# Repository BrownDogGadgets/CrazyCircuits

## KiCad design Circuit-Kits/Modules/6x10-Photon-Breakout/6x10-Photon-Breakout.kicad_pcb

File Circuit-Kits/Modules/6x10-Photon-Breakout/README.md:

<!--- start title --->
# 6x10 Photon Breakout Module v1.0
A Lego-compatible Crazy Circuits module

- Updated: 31 Jul 2018
- Website: http://browndoggadgets.com/
- Company: Brown Dog Gadgets
- License: All rights reserved.
<!--- end title --->

This breakout board is for use with the Particle Photon V016 and all pin-compatible boards. 

Powering it from the USB cable will output 5V and 3.3V. There are four three-pin servo headers.   

We recommend buying one 20-pin Harwin connector (P/N [M20-9992046](https://www.digikey.com/products/en?keywords=M20-9992046)) and breaking it into pieces to place the six male headers.

<!--- bom start --->
### Bill of Materials

|Ref|Qty|Description|Digikey PN|
|---|---|-----------|------|
|U1|1|PARTICLE PHOTON V016|1878-1000-ND|

<!--- bom end --->

### Manufacturing Notes

This board must be v-scored. Do not panelize with support tabs or mousebites.

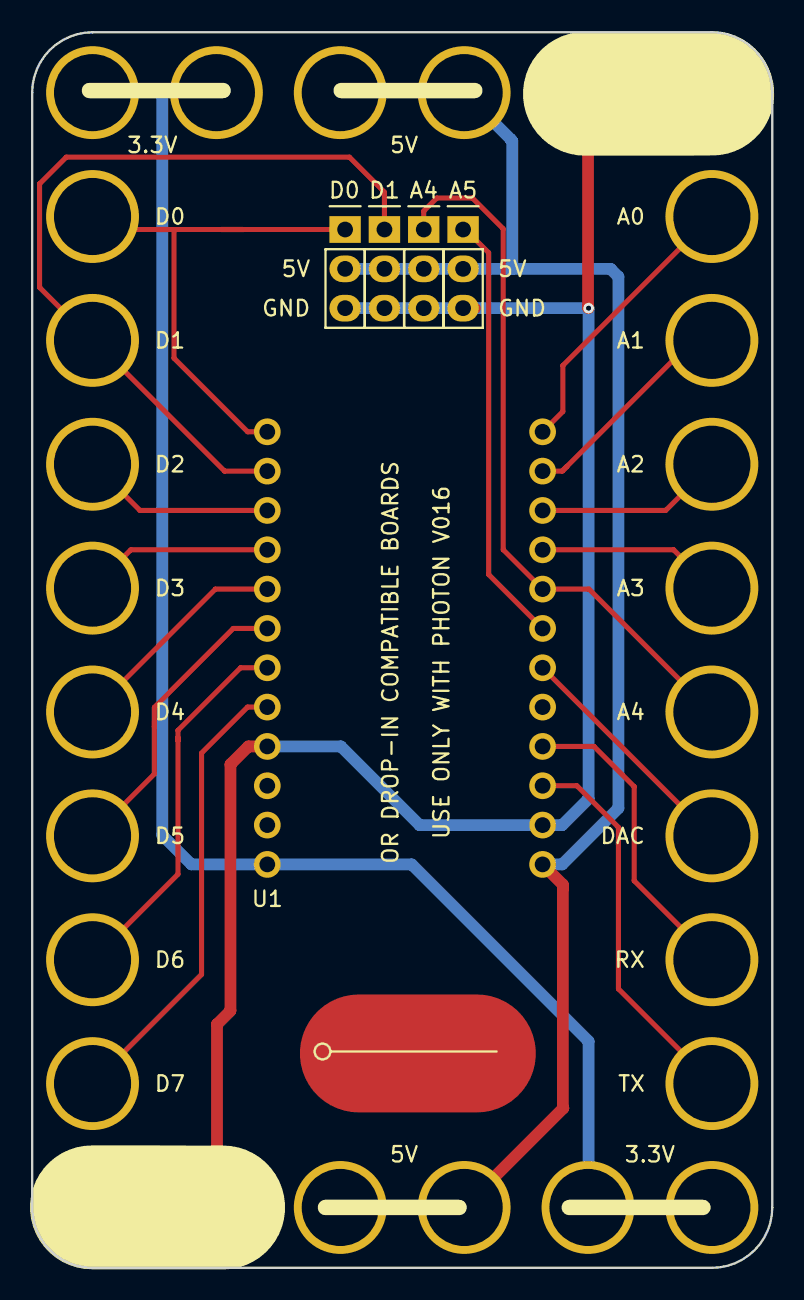
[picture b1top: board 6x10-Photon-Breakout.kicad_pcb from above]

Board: 2 copper layers, 47.8 x 79.8 mm, 6 parts (0 on the bottom side), 6 nets.

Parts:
J1, J2, J3: PWM; CONN-HEADER-STRAIGHT-P2.54MM-1x03
J4: Breakout; CONN-HEADER-STRAIGHT-P2.54MM-1x03
LOGO: BROWN DOG; LOGO-CRAZY-1x2
U1: PARTICLE-PHOTON-V016; PHOTON-V016-6x10

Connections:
5V: J1.VIN, J2.VIN, J3.VIN, J4.VIN, U1.5V, U1.VIN
/A4: J3.A4, U1.A4
/A5: J4.A5, U1.A5
/D0: J1.D0, U1.D0
/D1: J2.D1, U1.D1
GND: J1.GND, J2.GND, J3.GND, J4.GND, U1.GND

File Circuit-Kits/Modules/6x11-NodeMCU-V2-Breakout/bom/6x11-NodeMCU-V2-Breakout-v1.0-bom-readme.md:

|Ref|Qty|Description|Banggood PN|
|---|---|-----------|------|
|U1|1|NODEMCU LUA V2 ESP-12E DEV KIT|1097112|


|Ref|Qty|Description|Digikey PN|
|---|---|-----------|------|
|J1 J2 J3 J4|4|HEADER MALE 3POS TH 1x03 0.1IN|952-1902-ND|

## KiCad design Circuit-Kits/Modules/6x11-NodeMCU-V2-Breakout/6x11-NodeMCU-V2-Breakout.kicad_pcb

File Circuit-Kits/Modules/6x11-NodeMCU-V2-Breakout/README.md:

<!--- start title --->
# 6x11 NodeMCU V2 Breakout Module v1.0
A Lego-compatible Crazy Circuits module

- Updated: 18 Jul 2018

- Website: http://browndoggadgets.com/
- Company: Brown Dog Gadgets
- License: All rights reserved.
<!--- end title --->

The NodeMCU project calls this version of the board v1.0, but it's commonly called the V2 in production. 

This is the vendor we used: [Banggood P/N 1097112](https://www.banggood.com/NodeMcu-Lua-WIFI-Internet-Things-Development-Board-Based-ESP8266-CP2102-Wireless-Module-p-1097112.html)

Here's the documentation from NodeMCU, including a handy pinout diagram: [NodeMCU v1.0 docs](https://github.com/nodemcu/nodemcu-devkit-v1.0)

The module can be powered by plugging in USB or by applying 5V to the VIN input pin on the lower left. Don't expect to pull 5V out of the module: 5V is input only. This is a 3.3V module.

<!--- bom start --->
### Bill of Materials

|Ref|Qty|Description|Banggood PN|
|---|---|-----------|------|
|U1|1|NODEMCU LUA V2 ESP-12E DEV KIT|1097112|

|Ref|Qty|Description|Digikey PN|
|---|---|-----------|------|
|J1 J2 J3 J4|4|HEADER MALE 3POS TH 1x03 0.1IN|952-1902-ND|

<!--- bom end --->

### Manufacturing Notes

This board must be v-scored. Do not panelize with support tabs or mousebites.

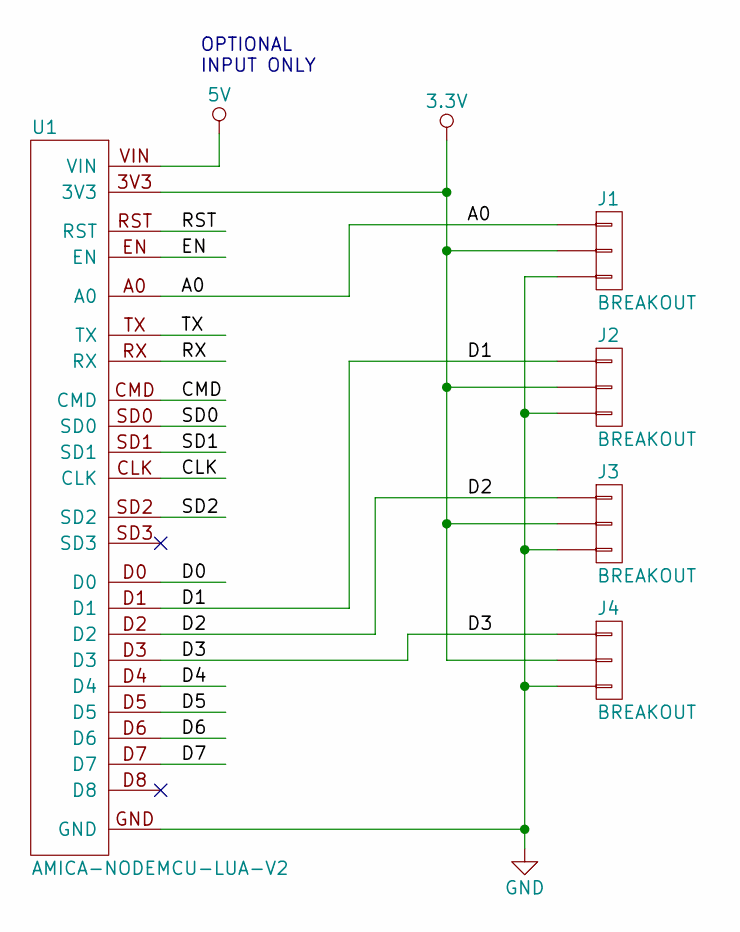
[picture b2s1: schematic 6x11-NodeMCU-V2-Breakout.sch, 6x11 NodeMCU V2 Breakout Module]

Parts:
J1, J2, J3, J4: BREAKOUT; CONN-HEADER-STRAIGHT-P2.54MM-1x03
U1: AMICA-NODEMCU-LUA-V2; NODEMCU-V2-6x11

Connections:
3.3V: J1.2, J2.2, J3.2, J4.2, U1.3V3
5V: U1.VIN
/A0: J1.1, U1.A0
/CLK: U1.CLK
/CMD: U1.CMD
/D0: U1.D0
/D1: J2.1, U1.D1
/D2: J3.1, U1.D2
/D3: J4.1, U1.D3
/D4: U1.D4
/D5: U1.D5
/D6: U1.D6
/D7: U1.D7
/EN: U1.EN
/RST: U1.RST
/RX: U1.RX
/SD0: U1.SD0
/SD1: U1.SD1
/SD2: U1.SD2
/TX: U1.TX
GND: J1.3, J2.3, J3.3, J4.3, U1.GND

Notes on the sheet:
OPTIONAL INPUT ONLY

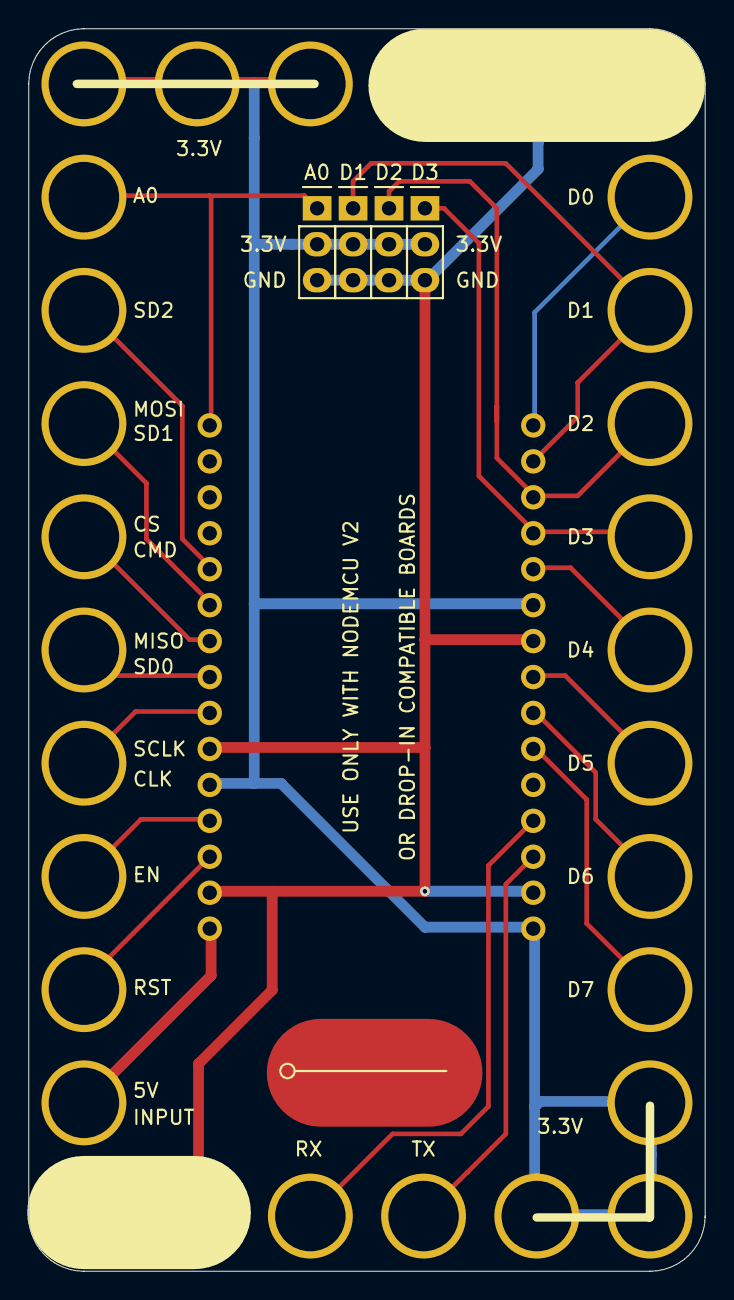
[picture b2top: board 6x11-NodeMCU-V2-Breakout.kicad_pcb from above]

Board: 2 copper layers, 47.8 x 87.8 mm, 6 parts (0 on the bottom side), 6 nets.

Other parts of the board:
LOGO: BROWN DOG; LOGO-CRAZY-1x2

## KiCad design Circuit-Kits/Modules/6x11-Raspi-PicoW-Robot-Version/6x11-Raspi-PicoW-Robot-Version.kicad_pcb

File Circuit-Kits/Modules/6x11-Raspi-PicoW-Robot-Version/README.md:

<!--- start title --->
# 5x11 Raspberry Pi PicoW Robot Breakout v1.6
A Lego-compatible Crazy Circuits module

- Updated: 24 Sep 2018
- Website: http://browndoggadgets.com/
- Company: Brown Dog Gadgets
- License: CERN Open Hardware License v1.2.
<!--- end title --->

This robot controller module comes with an Arduino Nano, four servo headers, and two analog headers. 

We recommend buying two 20-pin Harwin connectors (P/N [M20-9992046](https://www.digikey.com/products/en?keywords=M20-9992046)) and breaking it into pieces to place the six male headers.

<!--- bom start --->
## Bill of Materials

|Ref|Qty|Description|Digikey PN|
|---|---|-----------|------|
|J1-6|6|HEADER MALE 3POS TH 1x03 0.1IN|952-2264-ND|
|U1|1|Raspberry Pi PICO W Board|2648-SC0918CT-ND|

<!--- bom end --->

### Manufacturing Notes

This board must be v-scored. Do not panelize with support tabs or mousebites.

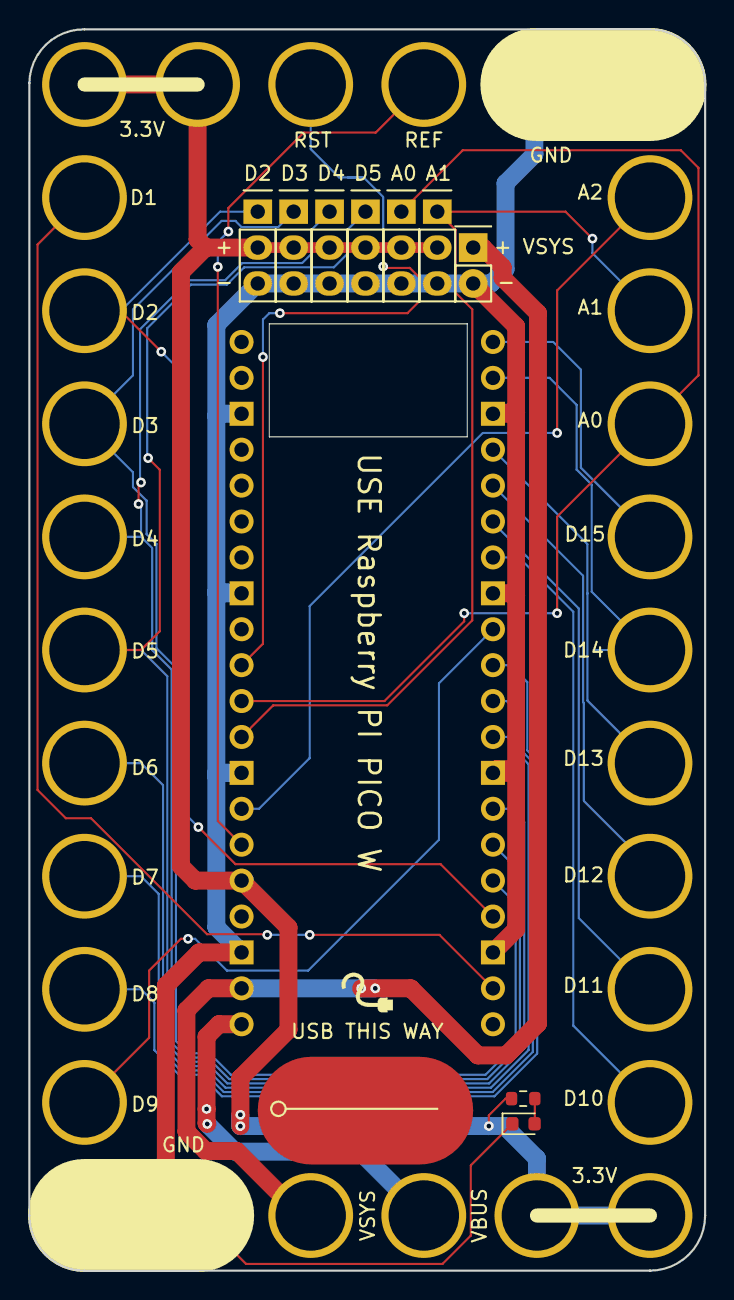
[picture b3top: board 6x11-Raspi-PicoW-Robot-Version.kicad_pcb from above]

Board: 2 copper layers, 47.8 x 87.8 mm, 13 parts (0 on the bottom side), 25 nets.

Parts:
D1: LED; LED_0603_1608Metric
J1, J2, J3, J4: PWM; CONN-HEADER-STRAIGHT-P2.54MM-1x03
J5, J6: ANALOG; CONN-HEADER-STRAIGHT-P2.54MM-1x03
J7: Conn_01x02; CONN-HEADER-STRAIGHT-P2.54MM-1x02
LOGO: BROWN DOG; LOGO-CRAZY-1x2
R1: 330; R_0603_1608Metric
Ref**: Val**; cable
U1: 6x11-PICOW; 6x11-PICO-ROBOT
U2: Pico W; RPi_Pico_SMD_TH

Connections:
3.3V: J1.2, J2.2, J3.2, J4.2, J5.2, J6.2, R1.1, U1.3V, U2.36
ADC0: J5.1, U1.A0, U2.31
ADC1: J6.1, U1.A1, U2.32
ADC2: U1.A2, U2.34
AREF: U1.REF, U2.35
GND: D1.1, J1.3, J2.3, J3.3, J4.3, J5.3, J6.3, J7.2, U1.GND, U2.3, U2.8, U2.13, U2.18, U2.23, U2.28, U2.33, U2.38
IO1: U1.TX1, U2.2
IO2: J1.1, U1.D2, U2.4
IO3: J2.1, U1.D3, U2.5
IO4: J3.1, U1.D4, U2.6
IO5: J4.1, U1.D5, U2.7
IO6: U1.D6, U2.9
IO7: U1.D7, U2.10
IO8: U1.D8, U2.11
IO9: U1.D9, U2.12
IO10: U1.D10, U2.14
IO11: U1.D11, U2.15
IO12: U1.D12, U2.16
IO13: U1.D13, U2.17
IO14: U1.D14, U2.19
IO15: U1.D15, U2.20
unnamed: D1.2, R1.2
RST: U1.RST, U2.30
VBUS: U1.VBUS, U2.40
VSYS: J7.1, U1.VSYS, U2.39

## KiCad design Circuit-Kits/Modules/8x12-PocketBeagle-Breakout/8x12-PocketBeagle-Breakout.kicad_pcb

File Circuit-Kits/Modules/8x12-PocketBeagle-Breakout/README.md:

<!--- start title --->
# 8x12 PocketBeagle Breakout v1.0
A Lego-compatible Crazy Circuits module

- Updated: 6 Aug 2018

- Website: http://browndoggadgets.com/
- Company: Brown Dog Gadgets
- License: CERN Open Hardware License v1.2
<!--- end title --->

Breakout board for the PocketBeagle.

<!--- bom start --->
### Bill of Materials

|Ref|Qty|Description|Digikey PN|
|---|---|-----------|------|
|J1 J2 J3 J4 J5|5|HEADER MALE 3POS TH 1x03 0.1IN|952-1902-ND|
|J6|1|POCKETBEAGLE|POCKETBEAGLE-SC-569-ND|

<!--- bom end --->

\newpage

### Manufacturing Notes

This board must be v-scored. Do not panelize with support tabs or mousebites.

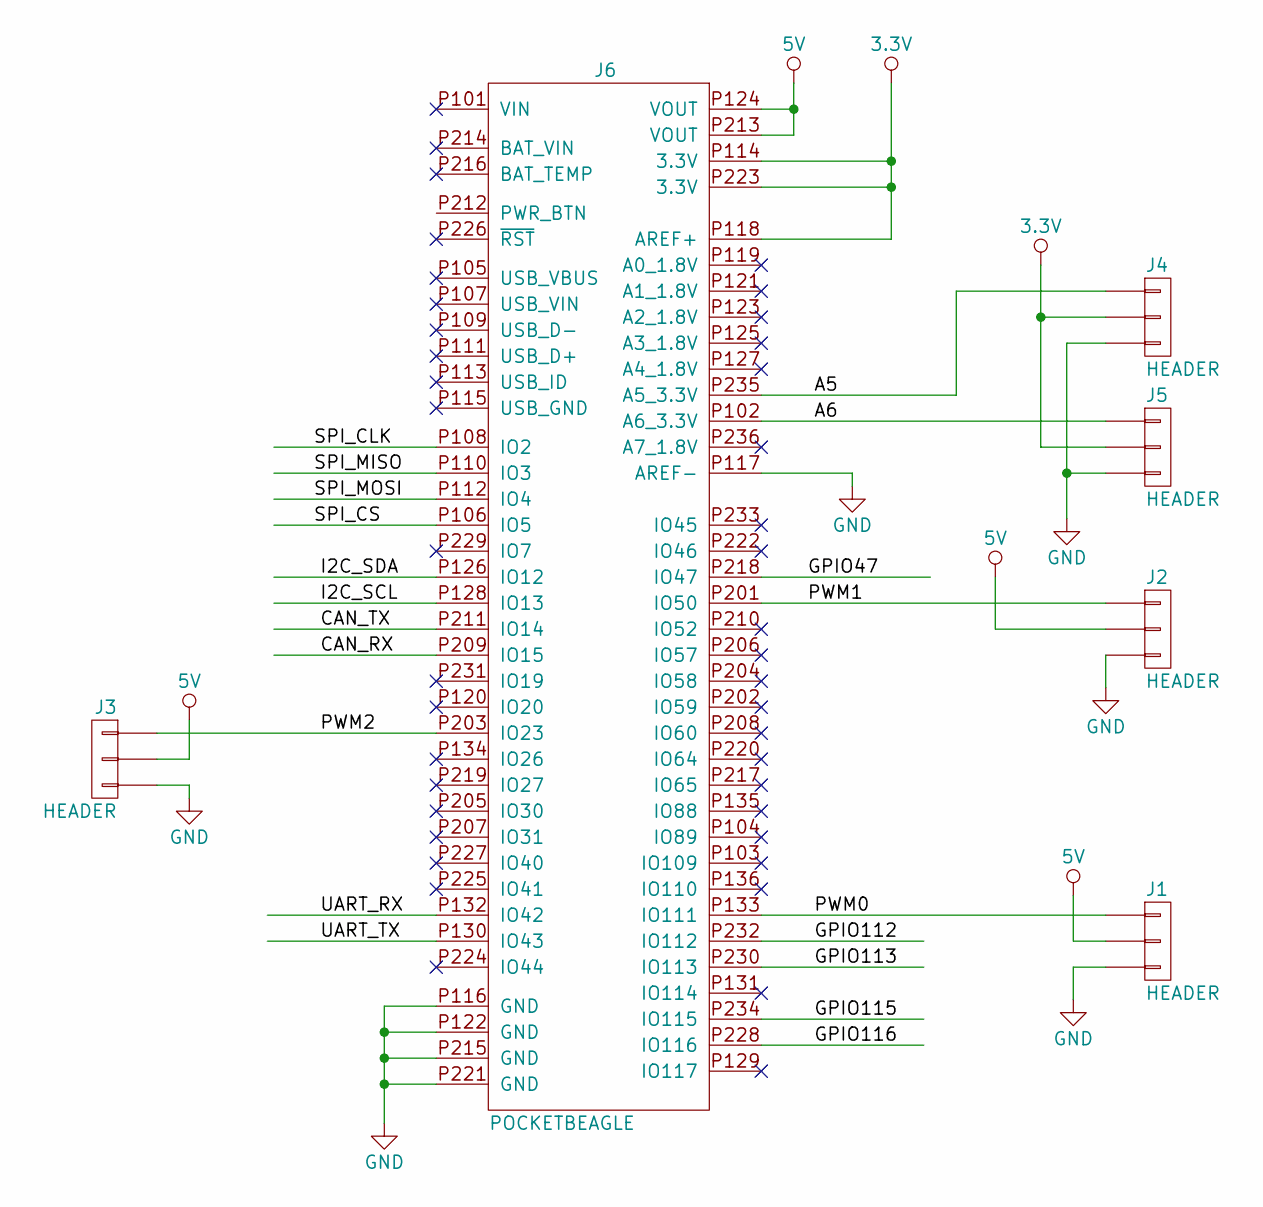
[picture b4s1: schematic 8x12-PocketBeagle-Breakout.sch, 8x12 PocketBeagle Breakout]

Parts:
J1, J2, J3, J4, J5: HEADER; CONN-HEADER-STRAIGHT-P2.54MM-1x03
J6: POCKETBEAGLE; POCKET-BEAGLE-8x12

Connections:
3.3V: J4.2, J5.2, J6.P114 (3.3V), J6.P118 (AREF+), J6.P223 (3.3V)
5V: J1.2, J2.2, J3.2, J6.P124 (VOUT), J6.P213 (VOUT)
/A5: J4.1, J6.P235 (A5_3.3V)
/A6: J5.1, J6.P102 (A6_3.3V)
/CAN_RX: J6.P209 (IO15)
/CAN_TX: J6.P211 (IO14)
/GPIO47: J6.P218 (IO47)
/GPIO112: J6.P232 (IO112)
/GPIO113: J6.P230 (IO113)
/GPIO115: J6.P234 (IO115)
/GPIO116: J6.P228 (IO116)
/I2C_SCL: J6.P128 (IO13)
/I2C_SDA: J6.P126 (IO12)
/PWM0: J1.1, J6.P133 (IO111)
/PWM1: J2.1, J6.P201 (IO50)
/PWM2: J3.1, J6.P203 (IO23)
/SPI_CLK: J6.P108 (IO2)
/SPI_CS: J6.P106 (IO5)
/SPI_MISO: J6.P110 (IO3)
/SPI_MOSI: J6.P112 (IO4)
/UART_RX: J6.P132 (IO42)
/UART_TX: J6.P130 (IO43)
GND: J1.3, J2.3, J3.3, J4.3, J5.3, J6.P116 (GND), J6.P117 (AREF-), J6.P122 (GND), J6.P215 (GND), J6.P221 (GND)

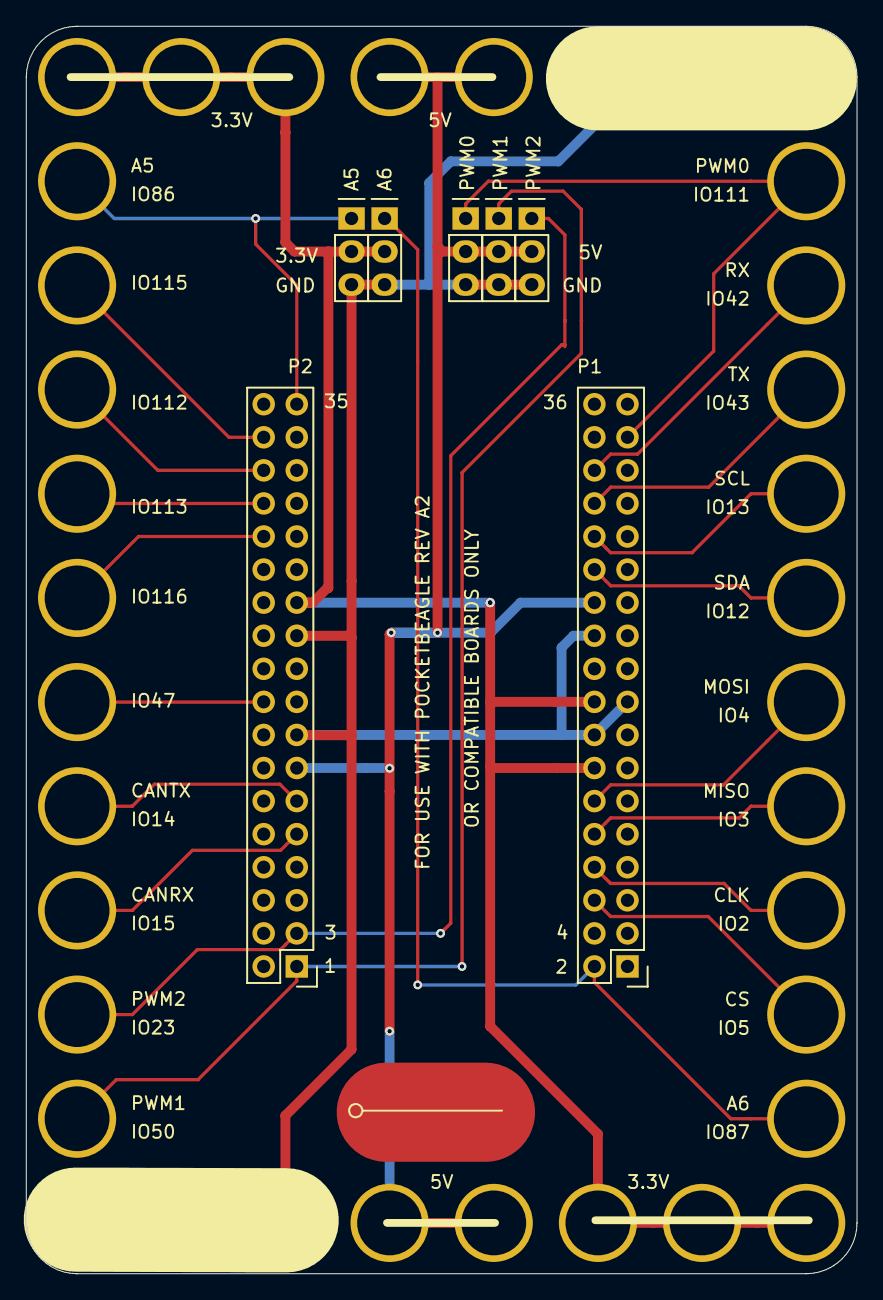
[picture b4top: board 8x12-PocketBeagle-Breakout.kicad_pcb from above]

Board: 2 copper layers, 63.8 x 95.8 mm, 7 parts (0 on the bottom side), 8 nets.

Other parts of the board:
LOGO: BROWN DOG; LOGO-CRAZY-1x2

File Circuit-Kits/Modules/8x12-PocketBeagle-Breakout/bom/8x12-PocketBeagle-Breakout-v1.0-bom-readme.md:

|Ref|Qty|Description|Digikey PN|
|---|---|-----------|------|
|J1 J2 J3 J4 J5|5|HEADER MALE 3POS TH 1x03 0.1IN|952-1902-ND|
|J6|1|POCKETBEAGLE|POCKETBEAGLE-SC-569-ND|
